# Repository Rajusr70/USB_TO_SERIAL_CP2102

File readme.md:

CP2102 USB to Serial Breakout Board
====================================
This breakout board enables you to connect to a standard USB A to B cable and communicate to your microcontroller via serial logic

Repository Contents
-----------------------------------------------------
* **/Hardware** - All Eagle design files (.brd, .sch)

License Information
--------------------------------
Distributed as-is; no warranty is given.

*www.technotics.in*

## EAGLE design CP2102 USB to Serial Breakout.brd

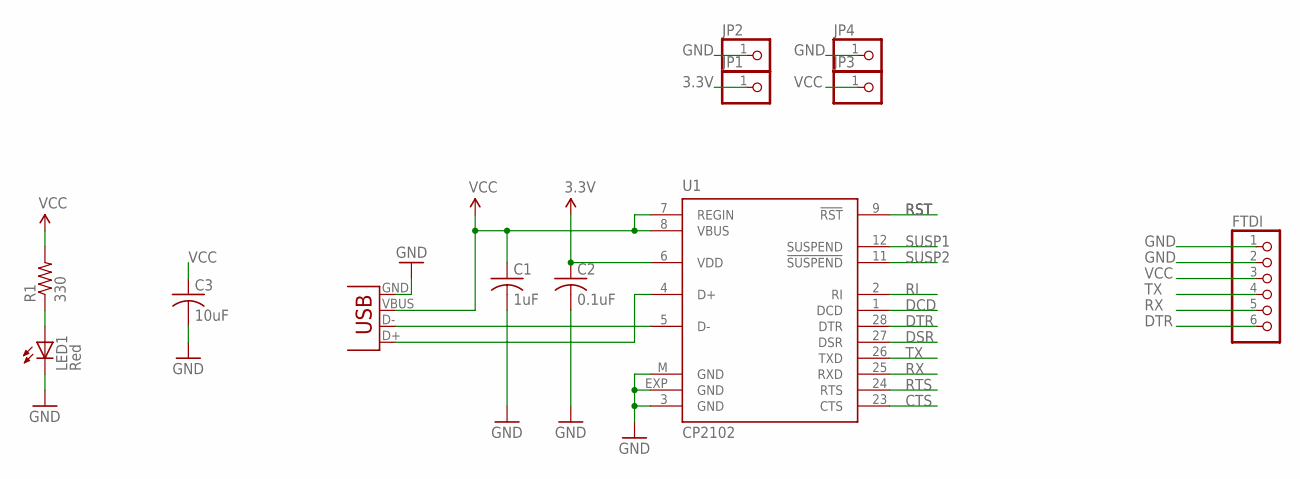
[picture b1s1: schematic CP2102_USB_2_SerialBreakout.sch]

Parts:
C1: 1uF; C1206
C2: 0.1uF; C1206
C3: 10uF; C1206
FTDI: PINHD-1X6CB; 1X06-CLEANBIG
JP1, JP2, JP3, JP4: PINHD-1X1; 1X01
LED1: Red; LED-1206
R1: 330; 1206
U1: CP2102; MLP28
X1: USBPTH; USB-B-PTH

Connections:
3.3V: C2.1, JP1.1, U1.6 (VDD)
CTS: U1.23 (CTS)
DCD: U1.1 (DCD)
DSR: U1.27 (DSR)
DTR: FTDI.6, U1.28 (DTR)
GND: C1.2, C2.2, C3.2, FTDI.1, FTDI.2, JP2.1, JP4.1, LED1.C, U1.3 (GND), U1.EXP (GND), U1.M (GND), X1.GND
unnamed: U1.5 (D-), X1.D-
unnamed: U1.4 (D+), X1.D+
unnamed: LED1.A, R1.1
RI: U1.2 (RI)
RST: U1.9 (!RST)
RTS: U1.24 (RTS)
RX: FTDI.5, U1.25 (RXD)
SUSP1: U1.12 (SUSPEND)
SUSP2: U1.11 (!SUSPEND)
TX: FTDI.4, U1.26 (TXD)
VCC: C1.1, C3.1, FTDI.3, JP3.1, R1.2, U1.7 (REGIN), U1.8 (VBUS), X1.VBUS

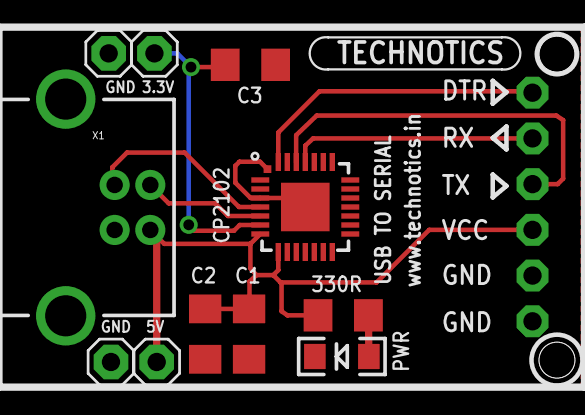
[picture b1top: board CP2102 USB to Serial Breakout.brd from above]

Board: 2 copper layers, 13 parts (0 on the bottom side), 9 nets.

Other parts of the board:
U$1: LOGONAME

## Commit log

2014-11-23 usb to serial board_v1
2014-11-23 cp2102usb2serial v1 ckt
2014-11-23 about the board and files
2014-11-23 update readme with product discription
2014-11-23 update readme with product discription.
